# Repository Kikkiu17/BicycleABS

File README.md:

# Il progetto
Alla base del progetto c'è il microcontrollore **STM32F103C6T6**. Ho usato poi un servo **MGR996R** collegato alle pastiglie del freno, l'encoder magnetico **AS5600** per la misura della velocità, un sensore hall **3144EUA** per la misura dell'angolo del freno e uno schermo OLED con controllore SH1106. Il firmware è stato tutto scritto da me, compreso il [driver per lo schermo OLED](https://github.com/Kikkiu17/STM32_SH1106), tranne il driver per l'encoder AS5600. Tutti i pezzi sono stati stampati in 3D in PETG, PLA e TPU con una stampante Bambu Lab A1 Mini.

In base all'angolo della maniglia del freno, il servo applica più o meno pressione alle pastiglie del freno, rallentando quindi la ruota e la bici. Quando la ruota si blocca, ad esempio se si frena tanto sullo sterrato, il microcontrollore rileva questa condizione e rilascia le pastiglie, in modo da sbloccare la ruota. Poi, riapplica pressione in modo da ricominciare a frenare e nel caso il ciclo continua.

Lo schermo OLED posto sul lato destro manubrio permette di vedere la velocità attuale della bici, i chilometri percorsi, il livello della batteria, lo stato delle luci (spente/accese/lampeggianti - la luce frontale, a cui ho tolto la batteria, era compresa con la bici, mentre la luce posteriore è fatta con due LED rossi) e se l'ABS si è attivato. Sul lato sinistro del manubrio invece è posto un pulsante che può essere usato per diverse cose. Se si fa una pressione breve si cambia la modalità delle luci (spente/accese/lampeggianti) in maniera ciclica. Se si fa una pressione lunga si entra nel menù, dal quale si possono modificare varie impostazioni (come l'angolo del servo, che quindi corrisponde alla pressione massima del freno, oppure la luminosità dello schermo), visualizzare diversi parametri di debug (come variabili interne dei TIMER del microcontrollore) e non (come la tensione della batteria).

# Costruzione - Hardware
Lo sviluppo dell'hardware è stato molto impegnativo. Il mio piano era modulare: sarei partito con la cosa più semplice, ovvero il supporto del servo, per fare un sistema **_brake by wire_**. In caso di successo, avrei continuato con il sensore dell'angolo della maniglia del freno (che d'ora in poi chiameremo **sensore freno**). In caso di successo, avrei continuato infine con il sensore di velocità della ruota. In questo modo avrei sprecato meno tempo possibile in caso di fallimento di qualche pezzo.

## Supporto e bracci servo
Per avvitare il supporto alla bici, ho sfruttato due buchi sul telaio apparentemente inutil in una posizione convenientemente vicina alle pastiglie del freno posteriore. Ho creato un supporto molto resistente e molto difficile da piegare in **PETG**, plastica adatta all'uso esterno (resistente ai raggi UV e al calore). Dopo ho realizzato dei bracci corti (in modo da massimizzare la coppia), da avvitare ai bracci del freno esistenti, **_print in place_**, ovvero che non necessitano di assemblaggio dopo la stampa (questo perché sono presenti due cerniere, difficili da fare resistenti e adatte all'assemblaggio). In questo modo il servo rimane ben saldo al telaio della bici e può fare tutta la forza che vuole.

## Sensore freno
Il sensore consiste in un magnete che ruota e una scheda con un chip che registra l'angolo del campo magnetico prodotto dal sensore. Non c'è però nessun punto comodo in cui montare né la parte fissa (il chip), né quella mobile (il magnete). Per il magnete quindi ho creato una sorta di morsa con dei gommini morbidi (quelli blu nella GIF) avvitata attorno alla maniglia del freno. Questa morsa ha un prolungamento su cui è situato il magnete, che si trova proprio sull'asse di rotazione della maniglia. Per il chip ho creato un supporto da avvitare al manubrio e che si estende fino a sopra il magnete, in modo da poter registrare il suo angolo. In base a quest'angolo, poi, determino l'angolo della maniglia e quindi quanto sto frenando. Dopo alcuni calcoli e controlli quest'angolo viene trasformato nell'angolo servo che viene direttamente inviato a quest'ultimo.

## Sensore di velocità
Il sensore di velocità comprende un semplice sensore **_hall_** (che rileva la presenza di un magnete o meno) e 30 magneti montati su un disco, a sua volta montato sulla ruota posteriore. Misurando quanti magneti vengono rilevati al secondo, si può determinare la velocità della ruota. Anche qui il problema è che non c'è nessun punto di montaggio comodo. Ho dovuto quindi creare il disco arancione in due pezzi in modo da poterlo mettere sull'asse di rotazione senza dover smontare l'intera ruota (il che significherebbe smontare anche il cambio... cosa che non avevo voglia di fare decine di volte) e per tenerlo fisso ad essa ho creato il pezzo nero che va ad avvitarsi dietro. In questo modo il pezzo arancione e il pezzo nero, avvitandosi, vanno a stringersi sui raggi del cerchio della ruota, effettivamente bloccandoli ad essa.

Il supporto del sensore **_hall_** è messo sull'asse della ruota e tenuto fermo con il dado originale che tiene fissa la ruota al telaio.

## Batteria
Ho anche creato un contenitore per una batteria LiPo 2S (7.4 V) che contiene anche un modulo per la ricarica della stessa. Ho voluto creare questo contenitore in modo da poter estrarre la batteria dalla bici in modo facile e veloce, così che posso portarla comodamente con me quando devo ricaricarla.

# Circuito elettronico
## Primo prototipo
Ho costruito il primo prototipo di circuito su una scheda millefori contemporaneamente allo sviluppo dei pezzi stampati in 3D. Dopo aver installato tutte le componenti e aver scritto parte del codice, ho realizzato che una scheda del genere non era adatta. Questo perché facendo pressione con il coperchio della scatola della scheda, oppure con qualche vibrazione (ad esempio passando dalla strada al marciapiede), il programma si bloccava e il servo rimaneva nella posizione di massima pressione. Dopo aver cercato per diverso tempo la causa del problema e non avendola trovata, ho deciso di abbandonare lo sviluppo su questa scheda. Questa però non è stata inutile perché mi ha permesso di testare le componenti e il programma, quindi sono passato allo sviluppo di una PCB (era solo un **_proof of concept_**).

## PCB
Ho creato quindi la PCB con tutti i vari MOSFET per poter controllare la luce frontale e posteriore (luce posteriore che si accende quando si frena, mentre rimane spenta quando non si frena), il servo e il sensore di velocità. Ho messo poi due connettori per collegare lo schermo OLED e il sensore freno via I²C al microcontrollore. Ho lasciato anche dello spazio per il convertitore DC-DC dalla tensione della batteria a 6 V, ovvero la tensione per il servo, aggiungendo poi un altro regolatore di tensione per trasformare questi 6 V in 3.3 V per il microcontrollore.

Ho fatto qualche errore, ovvero che le impronte dei MOSFET non erano corrette, quindi quando ho assemblato la PCB ho dovuto ruotare questi componenti di 90°... però funziona.

# Firmware
## Calcolo velocità
L'output del sensore hall sulla ruota è un'onda quadra con un certo periodo. Questo periodo idealmente dovrebbe essere in microsecondi, così la conversione in secondi sarebbe molto semplice. C'è una limitazione: i timer dell'STM32F103 sono a 16-bit, quindi il valore massimo è 65535 - se questi fossero microsecondi, il periodo massimo registrabile sarebbe di circa 65 millisecondi. Facendo $f_{mag}=\frac{1}{T_{hall}}=\frac{1}{0.065}=15.38\text{ Hz}$ otteniamo la frequenza di rilevamento dei magneti dal sensore. Dato che abbiamo 30 magneti: $f_{ruota}=\frac{f_{mag}}{30}=\frac{15.38}{30}=0.51\text{ Hz}$.

Questo è un moto circolare, quindi per calcolare la velocità tangenziale bisogna fare: $v_{ruota}=\frac{r\Delta\theta}{\Delta t}=r\Delta\theta f_{ruota}$. Visto che abbiamo il periodo di un'intera rotazione, consideriamo che l'arco sia la circonferenza della ruota: $\Delta\theta=\frac{arco}{raggio}=\frac{2\pi r}{r}=2\pi$, quindi la formula iniziale diventa: $v_{ruota}=2\pi rf_{ruota}$.

Ora possiamo finalmente vedere la velocità minima registrabile, col periodo massimo di 65 millisecondi, ovvero 0.51 Hz. Considerando il raggio della ruota $r=0.34\text{ m}$: $v_{ruota}=2\pi (0.34\text{ m})(0.51\text{ Hz})=1.08\text{ m/s}$ ovvero 3.9 km/h. Questa è una velocità minima un po' troppo alta e quindi sarebbe difficile rilevare quando la ruota è effettivamente ferma.

Dobbiamo quindi aumentare il periodo massimo registrabile. Fino ad ora, abbiamo considerato che un "tick" equivalga a un microsecondo, ma ora dobbiamo farlo valere di più: ad esempio, se 1 tick = 2 microsecondi, allora il periodo massimo registrabile sarebbe il doppio, ovvero 130 millisecondi e utilizzando la formula di prima la velocità minima sarebbe di 1.97 km/h che è già più accettabile. Per fare questo calcolo nel software, dobbiamo considerare la frequenza del clock del timer, che è uguale per tutte le periferiche `APB1` e in questo caso è di `64 MHz`. Il valore di ogni tick è dato dalla frequenza di clock del timer diviso il "prescaler" `PSC`. Quindi, se il prescaler fosse di 128, avremmo $f_{TIM}=\frac{64000000}{128}=500\text{ kHz}$ quindi il tick sarebbe di 2 microsecondi. Ora dividiamo la frequenza di ogni tick per il numero di tick registrati ($k_{hall}$) e otteniamo la frequenza dei magneti.

Quindi:

$f_{TIM}=\frac{f_{APB1}}{PSC}$

$f_{mag}=\frac{f_{TIM}}{k_{hall}}$

$f_{ruota}=\frac{f_{mag}}{30}=\frac{\frac{f_{TIM}}{k_{hall}}}{30}=\frac{\frac{\frac{f_{APB1}}{PSC}}{k_{hall}}}{30}$ -> questa è infine, facendo qualche semplificazione, la formula usata nel programma, in C: `freq = ((float)(apb1_timer_clock / 10 / ((TIM2->PSC + 1) / 1000)) / (float)period) / 30.0` da cui si ricava la velocità.
## Rilevamento blocco
Ci sono due timer in azione: il primo è quello che è stato usato finora per calcolare la velocità della ruota. Il secondo viene usato per il rilevamento del blocco di essa. Il secondo timer ha una frequenza di 20 Hz, quindi viene controllato se la ruota è bloccata ogni 50 ms. Ogni 50 ms, quindi, il secondo timer controlla il periodo del primo timer: se questo è troppo alto, ovvero più alto del periodo del secondo timer, significa che la ruota ha rallentato molto, quindi si può considerare che stia scivolando. Inoltre, il primo timer, ogni volta che il sensore hall rileva un magnete, resetta il valore del secondo timer, quindi il rilevamento del blocco è migliore. L'ABS, quindi, se la ruota scivola, si attiva.

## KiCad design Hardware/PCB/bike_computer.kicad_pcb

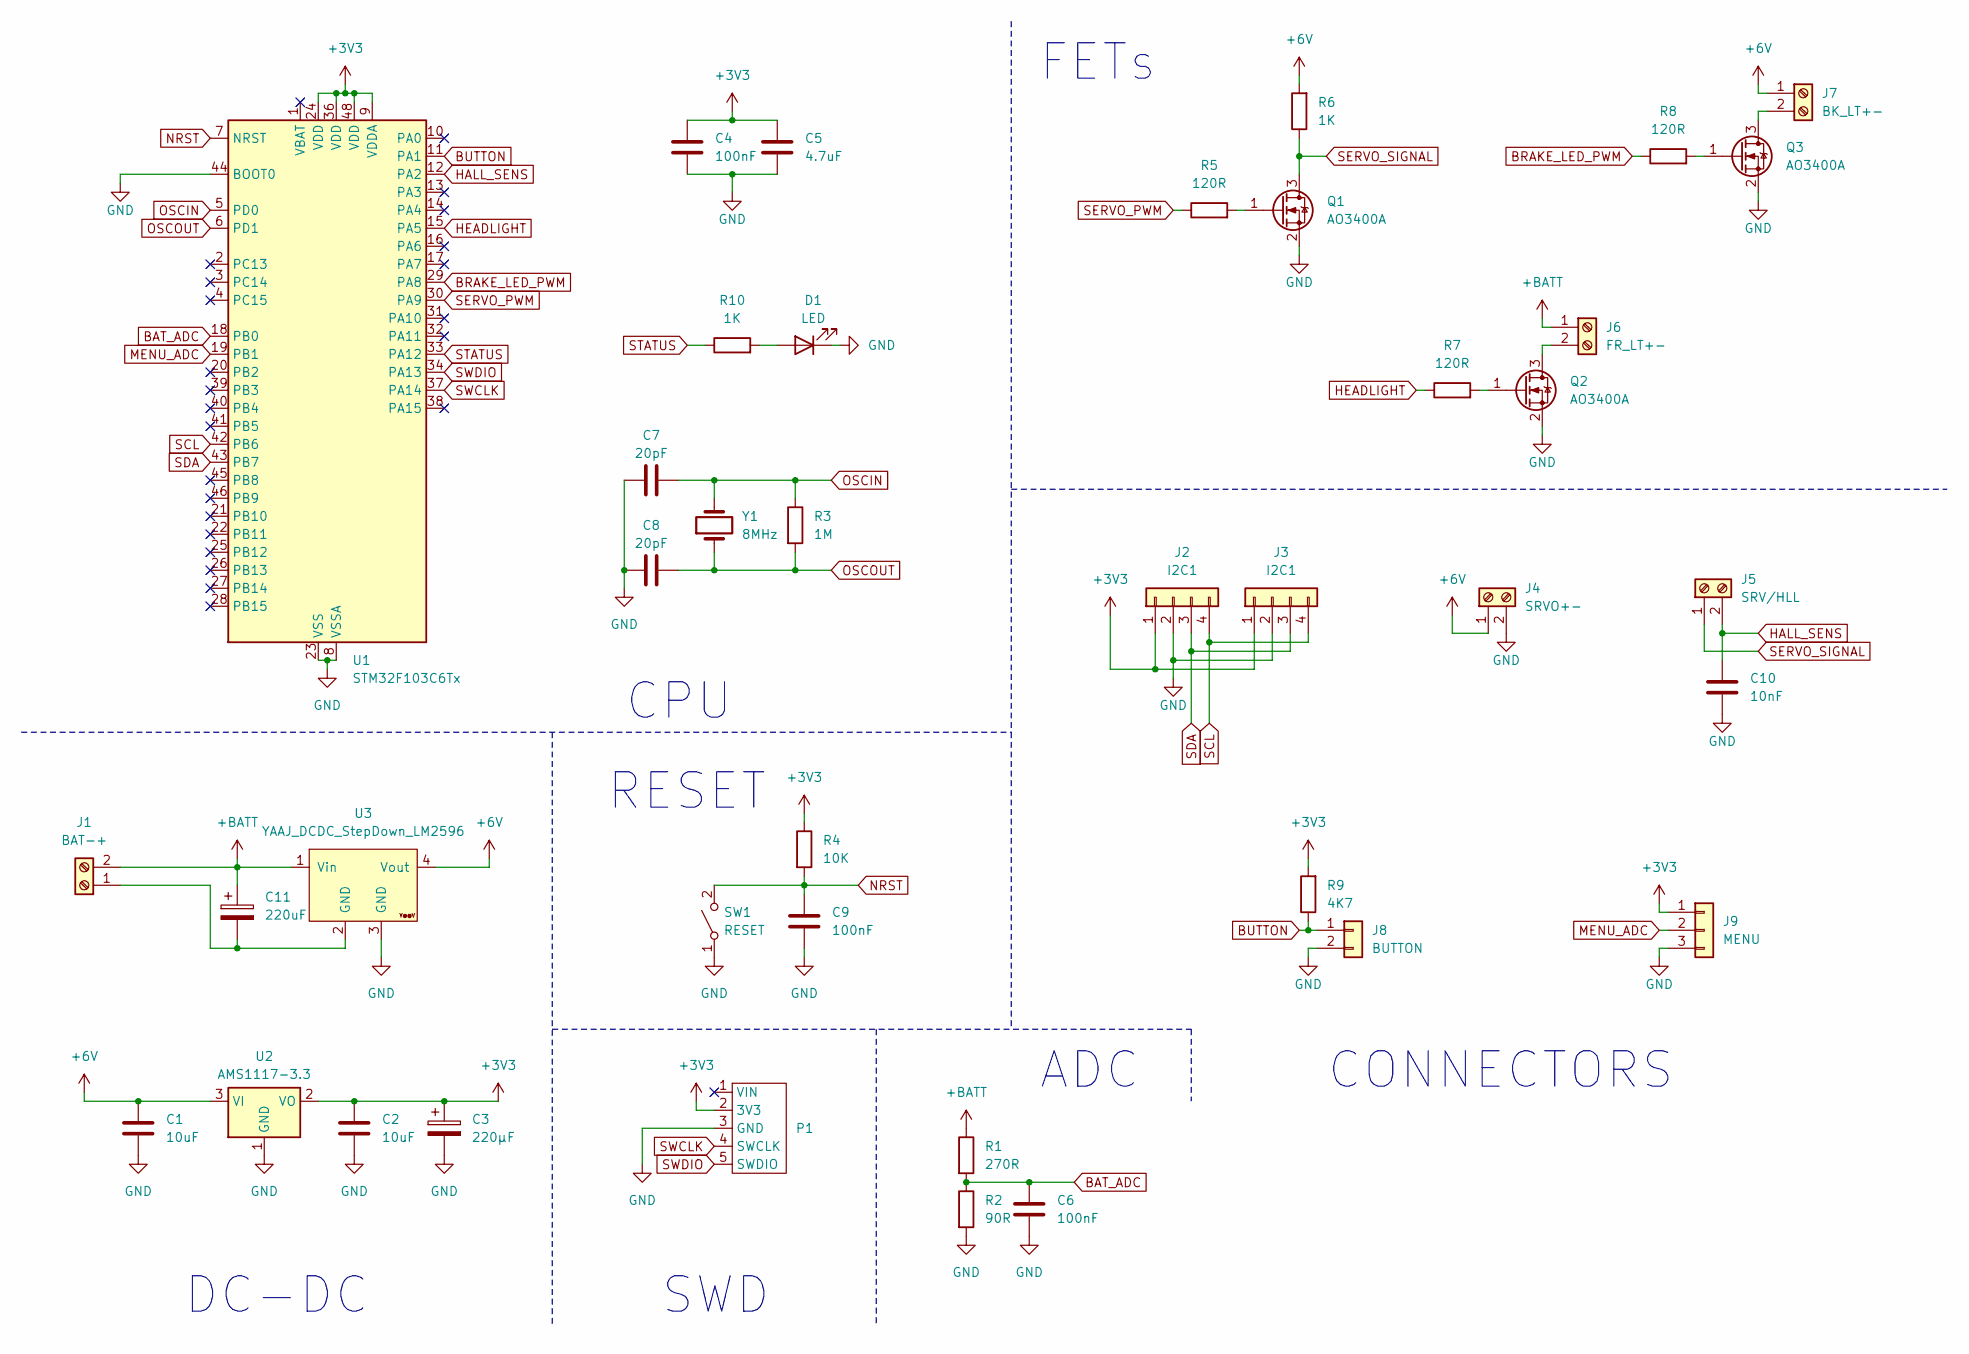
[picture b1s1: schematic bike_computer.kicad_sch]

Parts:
C1, C2: 10uF; C_0603_1608Metric
C3: 220µF; CP_Radial_D4.0mm_P1.50mm
C4, C6, C9: 100nF; C_0603_1608Metric
C5: 4.7uF; C_0603_1608Metric
C7, C8: 20pF; C_0603_1608Metric
C10: 10nF; C_0603_1608Metric
C11: 220uF; CP_Radial_D4.0mm_P1.50mm
D1: LED; LED_0603_1608Metric
J1: BAT-+; screw_2p_small
J2, J3: I2C1; JST_EH_B4B-EH-A_1x04_P2.50mm_Vertical
J4: SRVO+-; screw_2p_small
J5: SRV/HLL; screw_2p_small
J6: FR_LT+-; screw_2p_small
J7: BK_LT+-; screw_2p_small
J8: BUTTON; JST_EH_B2B-EH-A_1x02_P2.50mm_Vertical
J9: MENU; JST_EH_B3B-EH-A_1x03_P2.50mm_Vertical
P1: stm_headers
Q1, Q2, Q3: AO3400A; SOT-23
R1: 270R; R_0603_1608Metric
R2: 90R; R_0603_1608Metric
R3: 1M; R_0603_1608Metric
R4: 10K; R_0603_1608Metric
R5, R7, R8: 120R; R_0603_1608Metric
R6, R10: 1K; R_0603_1608Metric
R9: 4K7; R_0603_1608Metric
SW1: RESET; SW_PUSH_6mm
U1: STM32F103C6Tx; LQFP-48_7x7mm_P0.5mm
U2: AMS1117-3.3; SOT-223-3_TabPin2
U3: YAAJ_DCDC_StepDown_LM2596
Y1: 8MHz; Crystal_HC49-4H_Vertical

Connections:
+3V3: C2.1, C3.1, C4.1, C5.1, J2.1, J3.1, J9.1, P1.2 (3V3), R4.1, R9.2, U1.9 (VDDA), U1.24 (VDD), U1.36 (VDD), U1.48 (VDD), U2.2 (VO)
+6V: C1.1, J4.1, J7.1, R6.2, U2.3 (VI), U3.4 (Vout)
+BATT: C11.1, J1.2, J6.1, R1.1, U3.1 (Vin)
BAT_ADC: C6.1, R1.2, R2.1, U1.18 (PB0)
BRAKE_LED_PWM: R8.1, U1.29 (PA8)
BUTTON: J8.1, R9.1, U1.11 (PA1)
GND: C1.2, C2.2, C3.2, C4.2, C5.2, C6.2, C7.1, C8.1, C9.2, C10.2, D1.1 (K), J2.2, J3.2, J4.2, J8.2, J9.3, P1.3 (GND), Q1.2 (S), Q2.2 (S), Q3.2 (S), R2.2, SW1.1 (A), U1.8 (VSSA), U1.23 (VSS), U1.35 (VSS), U1.44 (BOOT0), U1.47 (VSS), U2.1 (GND), U3.3 (GND)
HALL_SENS: C10.1, J5.2, U1.12 (PA2)
HEADLIGHT: R7.1, U1.15 (PA5)
MENU_ADC: J9.2, U1.19 (PB1)
NRST: C9.1, R4.2, SW1.2 (B), U1.7 (NRST)
unnamed: C11.2, J1.1, U3.2 (GND)
unnamed: D1.2 (A), R10.2
unnamed: Q1.1 (G), R5.2
unnamed: J6.2, Q2.3 (D)
unnamed: Q2.1 (G), R7.2
unnamed: J7.2, Q3.3 (D)
unnamed: Q3.1 (G), R8.2
OSCIN: C7.2, R3.1, U1.5 (PD0), Y1.2
OSCOUT: C8.2, R3.2, U1.6 (PD1), Y1.1
SCL: J2.4, J3.4, U1.42 (PB6)
SDA: J2.3, J3.3, U1.43 (PB7)
SERVO_PWM: R5.1, U1.30 (PA9)
SERVO_SIGNAL: J5.1, Q1.3 (D), R6.1
STATUS: R10.1, U1.33 (PA12)
SWCLK: P1.4 (SWCLK), U1.37 (PA14)
SWDIO: P1.5 (SWDIO), U1.34 (PA13)

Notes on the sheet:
FETs
CPU
RESET
ADC
DC-DC
SWD
CONNECTORS

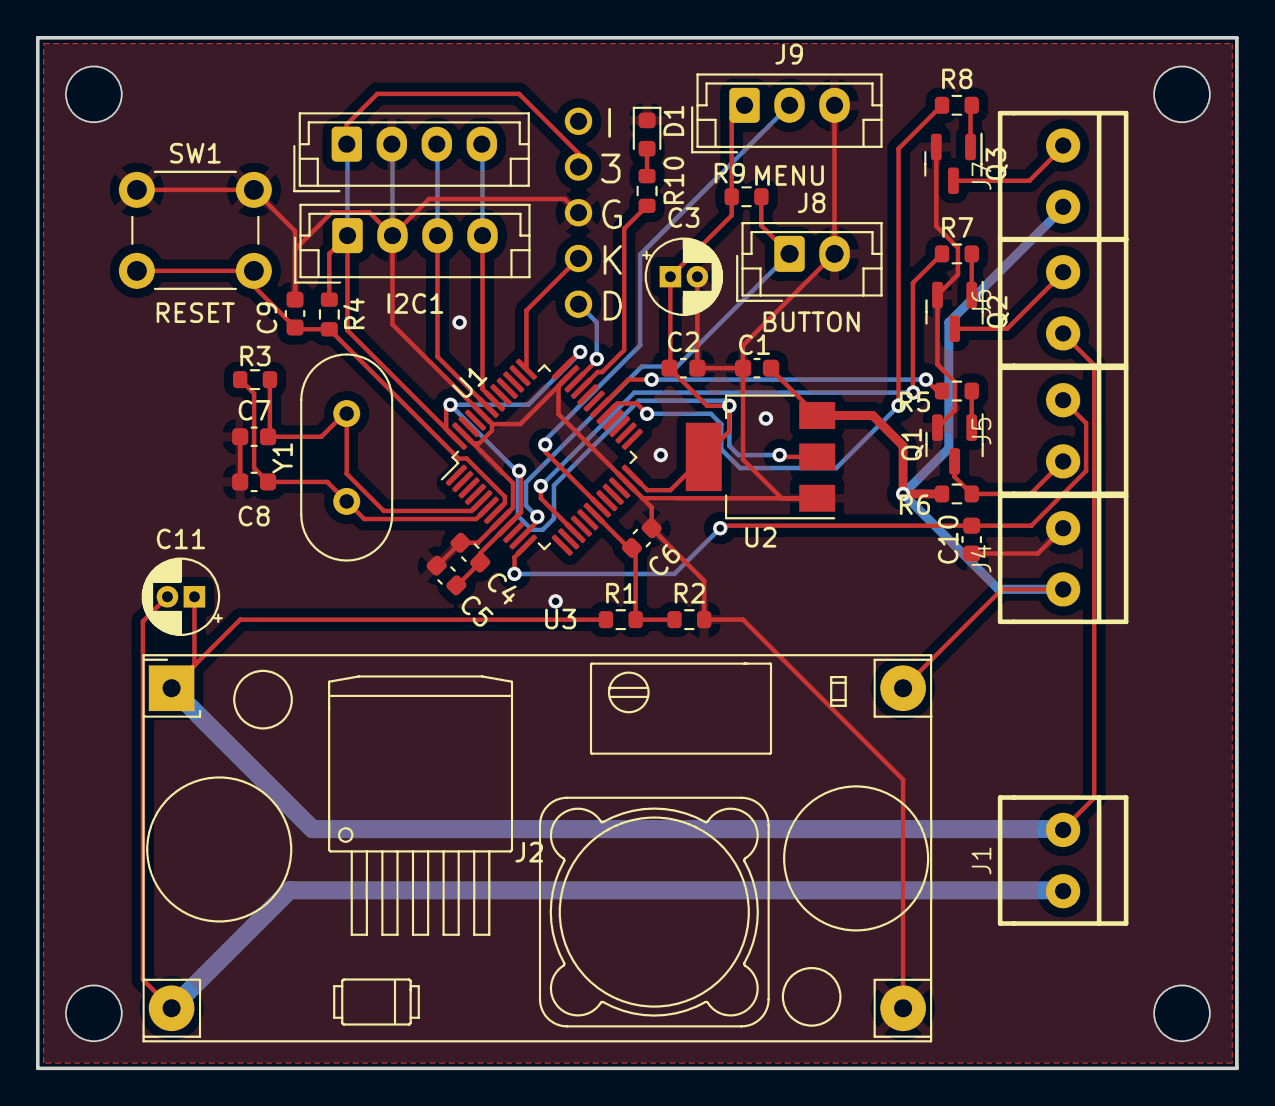
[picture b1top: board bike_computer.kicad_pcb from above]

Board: 2 copper layers, 66.6 x 57.3 mm, 40 parts (0 on the bottom side), 27 nets.

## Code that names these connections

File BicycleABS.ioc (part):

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Mcu.Name=STM32F103C(4-6)Tx
Mcu.Package=LQFP48
Mcu.UserName=STM32F103C6Tx
PA1.GPIOParameters=GPIO_PuPd,GPIO_Label
PA1.GPIO_Label=BTN_IN
PA1.GPIO_PuPd=GPIO_PULLUP
PA1.Signal=GPIO_Input
PA13.Mode=Serial_Wire
PA13.Signal=SYS_JTMS-SWDIO
PA14.Mode=Serial_Wire
PA14.Signal=SYS_JTCK-SWCLK
PA2.GPIOParameters=GPIO_PuPd,GPIO_Label
PA2.GPIO_Label=HALL_IN
PA2.GPIO_PuPd=GPIO_PULLUP
PA2.Signal=S_TIM2_CH3
PA5.GPIOParameters=GPIO_Label
PA5.GPIO_Label=FRONT_LIGHTS
PA5.Signal=GPIO_Output
PA8.GPIOParameters=GPIO_Label
PA8.GPIO_Label=BRAKE_LIGHT
PA8.Signal=S_TIM1_CH1
PA9.GPIOParameters=GPIO_Label
PA9.GPIO_Label=SERVO_OUT
PA9.Signal=S_TIM1_CH2
PB0.GPIOParameters=GPIO_Label
PB0.GPIO_Label=BAT_ADC
PB0.Signal=ADCx_IN8
PB6.Mode=I2C
PB6.Signal=I2C1_SCL
PB7.Mode=I2C
PB7.Signal=I2C1_SDA
PC13-TAMPER-RTC.GPIOParameters=GPIO_Label
PC13-TAMPER-RTC.GPIO_Label=BOARD_LED
PC13-TAMPER-RTC.Signal=GPIO_Output
PD0-OSC_IN.Mode=HSE-External-Clock-Source
PD0-OSC_IN.Signal=RCC_OSC_IN
PD1-OSC_OUT.Mode=HSE-External-Clock-Source
PD1-OSC_OUT.Signal=RCC_OSC_OUT
RCC.SYSCLKFreq_VALUE=64000000
RCC.SYSCLKSource=RCC_SYSCLKSOURCE_PLLCLK
board=custom

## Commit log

2025-03-11 Caricamento iniziale
2025-05-04 Immagini e readme
2025-05-04 Altre gif e immagini
2025-05-04 Gif sistemata
2025-05-04 Immagini 3D sistemate
